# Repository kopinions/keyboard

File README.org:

* Keyboard

** 键盘布局
[[file:assets/imgs/layout.jpg]]

** 硬件

硬件部分主要包含电路原理图，以及电路板设计图。
** 软件（固件）

软件部分主要包含 基于 esp-idf 实现的 esp32 mcu 的键盘主控固件。

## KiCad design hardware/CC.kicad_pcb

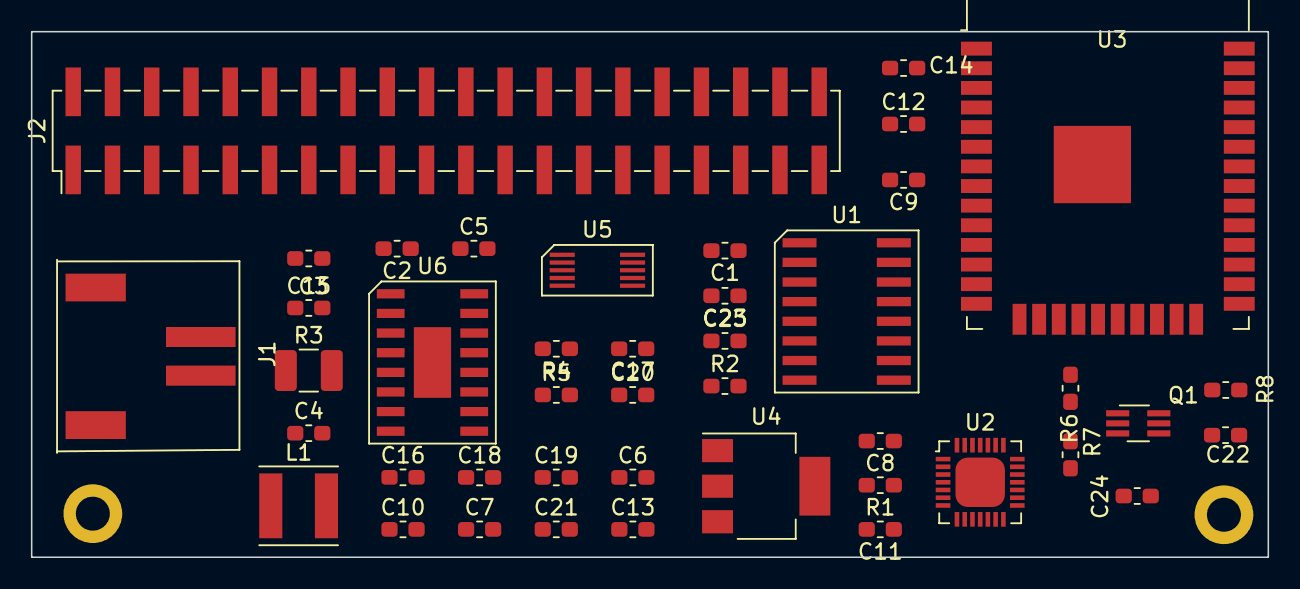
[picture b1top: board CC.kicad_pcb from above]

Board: 2 copper layers, 80.0 x 34.0 mm, 46 parts (1 on the bottom side), 55 nets, no tracks yet.

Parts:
C1: 103; C_0603_1608Metric_Pad1.05x0.95mm_HandSolder
C2, C5, C6, C7, C12, C17, C18, C23: 10uf; C_0603_1608Metric_Pad1.05x0.95mm_HandSolder
C3, C4, C8, C9, C10, C14, C16, C22, C24, C25: 104; C_0603_1608Metric_Pad1.05x0.95mm_HandSolder
C11: 4.7uf; C_0603_1608Metric_Pad1.05x0.95mm_HandSolder
C13: 2.2uf; C_0603_1608Metric_Pad1.05x0.95mm_HandSolder
C15: 4.7nf; C_0603_1608Metric_Pad1.05x0.95mm_HandSolder
C19, C20, C21: 22uf; C_0603_1608Metric_Pad1.05x0.95mm_HandSolder
H1, H2: MountingHole; MountingHole_2.2mm_M2_DIN965_Pad
J1: Conn_01x02_Female; JST_XH_S2B-XH-A-1_1x02_P2.50mm_Horizontal
J2: Conn_02x20_Odd_Even; PinHeader_2x20_P2.54mm_Vertical_SMD
L1: 1uH; L_5x5x2
Q1: Q_DUAL_NPN; SOT-363_SC-70-6_Handsoldering
R1: 22.1K; R_0603_1608Metric_Pad1.05x0.95mm_HandSolder
R2: 47.5K; R_0603_1608Metric_Pad1.05x0.95mm_HandSolder
R3: R010; R_1210_3225Metric_Pad1.42x2.65mm_HandSolder
R4: 2R0; R_0603_1608Metric_Pad1.05x0.95mm_HandSolder
R5: 102; R_0603_1608Metric_Pad1.05x0.95mm_HandSolder
R6, R7: 10K; R_0603_1608Metric_Pad1.05x0.95mm_HandSolder
R8: 10k; R_0603_1608Metric_Pad1.05x0.95mm_HandSolder
SW1: SW-2P; SW_DIP_SPSTx02_Slide_6.7x6.64mm_W8.61mm_P2.54mm_LowProfile
U1: CH9328
U2: CP2102N-A01-GQFN28; QFP-28_5x5_Pitch0.5mm
U3: ESP32-WROOM-32D; ESP32-WROOM-32
U4: AMS1117-3.3; SOT-223-3_TabPin2
U5: BL1530-DPDT; BL1530
U6: IP5108

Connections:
+BATT: C2.1, C3.1, J1.2, R3.2, U6.16
/ACT: U1.16, U3.22
/CAPS: J2.38, U3.20
/COL1: J2.13, U3.24
/COL2: J2.15, U3.26
/COL3: J2.17, U3.29
/COL4: J2.19, U3.14
/COL5: J2.21, U3.16
/COL6: J2.23, U3.13
/COL7: J2.25, U3.23
/COL8: J2.27, U3.27
/COL9: J2.29, U3.28
/COL10: J2.31, U3.30
/COL11: J2.33, U3.31
/COL12: J2.35, U3.33
/COL13: J2.37, U3.36
/COL14: J2.39, U3.37
/COL15: J2.40, U3.10
/DTR: Q1.4, R6.2, U2.28
/EN: C24.1, Q1.6, R8.2, SW1.3, U3.3
/FD+: U2.4, U5.2
/FD-: U2.5, U5.8
/FRXD: U2.25, U3.18
/FTXD: U2.26, U3.17
/IO0: C22.1, Q1.3, SW1.4, U3.25, U5.1
/KD+: U1.6, U5.3
/KD-: U1.7, U5.9
/KRXD: U1.3, U3.34
/KTXD: U1.2, U3.35
/L1: J2.6, U3.21, U6.9
/L2: J2.4, U3.5, U6.10
/L3: J2.2, U3.4, U6.11
/LX: C15.1, L1.2, U6.3, U6.4
/ROW1: J2.1, U3.11
/ROW2: J2.3, U3.12
/ROW3: J2.5, U3.8
/ROW4: J2.7, U3.9
/ROW5: J2.9, U3.6
/ROW6: J2.11, U3.7
/RTS: Q1.1, R7.2, U2.24
/SCLK: J2.36, U3.19
/USBD+: J2.32, U5.4
/USBD-: J2.30, U5.10
GND: C1.1, C2.2, C3.2, C4.2, C5.2, C6.2, C7.2, C8.1, C9.1, C10.2, C11.2, C12.2, C13.1, C14.1, C17.2, C20.2, C22.2, C23.2, C24.2, C25.1, J1.1, J2.10, J2.12, J2.14, J2.16, J2.18, J2.20, J2.22, J2.24, J2.26, J2.34, R2.2, R5.2, SW1.1, SW1.2, U1.8, U1.11, U2.3, U2.29, U3.1, U3.15, U3.38, U3.39, U4.1, U5.5, U5.7, U6.2, U6.8, U6.14, U6.15, U6.17
unnamed: C1.2, U1.5
unnamed: C4.1, C6.1, L1.1, R3.1, U6.1
unnamed: C5.1, R4.2
unnamed: C13.2, U6.12, U6.13
unnamed: C16.2, C18.2, C19.2, C21.2
unnamed: Q1.2, R6.1
unnamed: Q1.5, R7.1
unnamed: R1.2, R2.1, U2.8
VBUS: C7.1, C10.1, J2.28, R1.1, R4.1, R5.1, U6.7
VDD5V: C15.2, C16.1, C17.1, C18.1, C19.1, C21.1, U4.3, U6.5, U6.6
VDD33: C8.2, C9.2, C11.1, C12.1, C14.2, C20.1, C23.1, C25.2, J2.8, R8.1, U1.12, U1.13, U1.14, U1.15, U2.6, U2.7, U3.2, U4.2, U5.6

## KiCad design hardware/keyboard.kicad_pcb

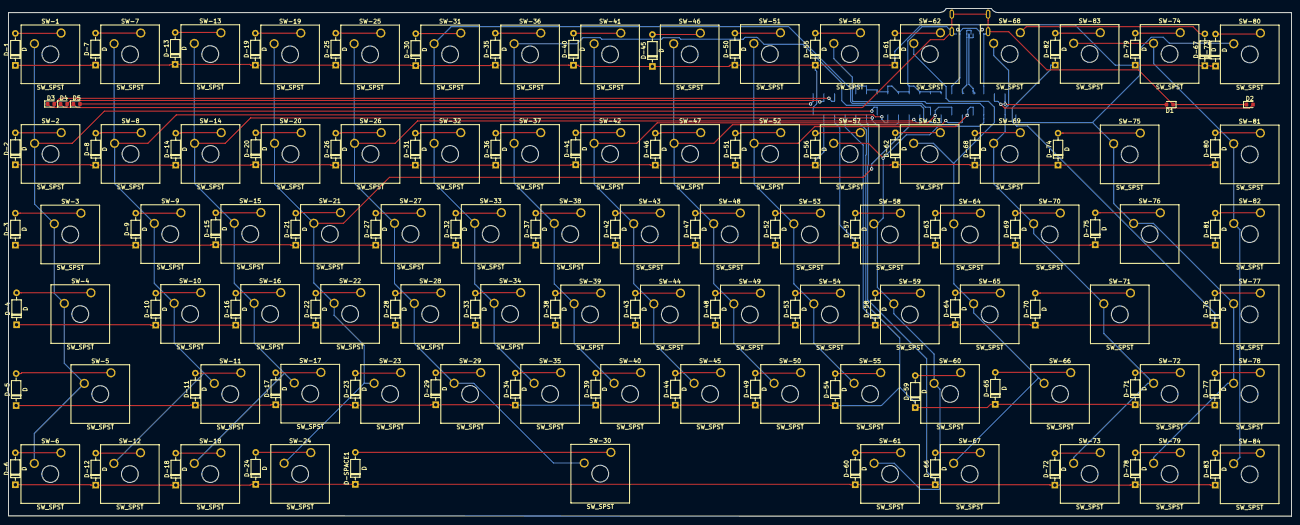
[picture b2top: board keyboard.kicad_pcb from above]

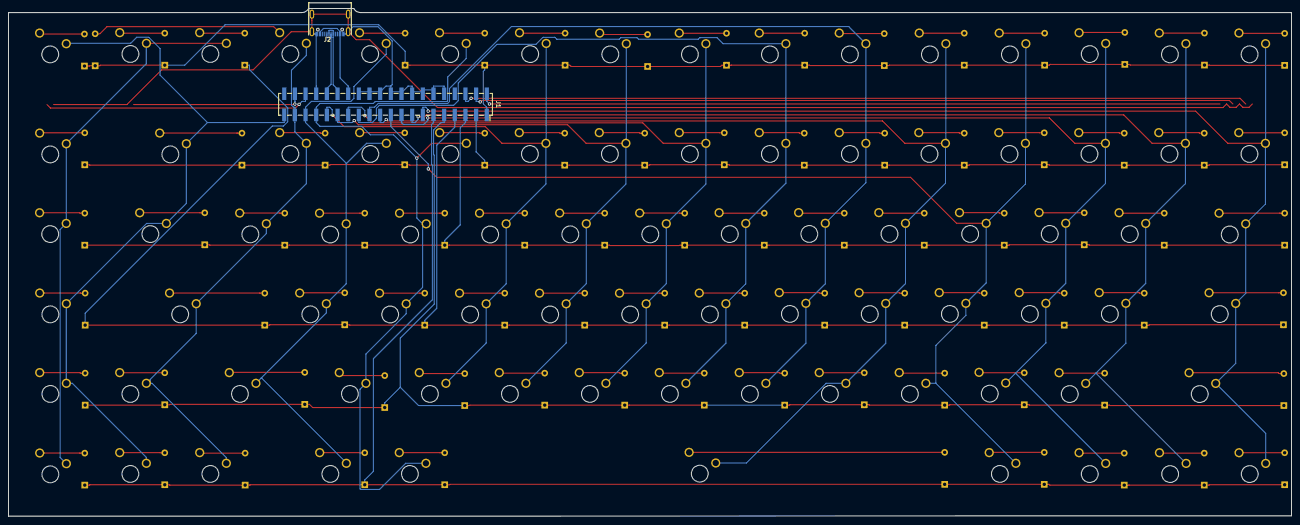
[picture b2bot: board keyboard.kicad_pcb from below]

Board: 2 copper layers, 305.7 x 121.0 mm, 175 parts (2 on the bottom side), 112 nets.

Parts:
D1, D2, D3, D4, D5: D; LED_0603_1608Metric
D-1, D-2, D-3, D-4, D-5, D-6, D-7, D-8, D-9, D-10, D-11, D-12, D-13, D-14, D-15, D-16, D-17, D-18, D-19, D-20, D-21, D-22, D-23, D-24, D-25, D-26, D-27, D-28, D-29, D-30, D-31, D-32, D-33, D-34, D-35, D-36, D-37, D-38, D-39, D-40, D-41, D-42, D-43, D-44, D-45, D-46, D-47, D-48, D-49, D-50, D-51, D-52, D-53, D-54, D-55, D-56, D-57, D-58, D-59, D-60, D-61, D-62, D-63, D-64, D-65, D-66, D-67, D-68, D-69, D-70, D-71, D-72, D-73, D-74, D-75, D-76, D-77, D-78, D-79, D-80, D-81, D-82, D-83: D; D_DO-35_SOD27_P7.62mm_Horizontal
D-SPACE1: D; D_DO-35_SOD27_P7.62mm_Horizontal
J1: Conn_02x20_Odd_Even; PinSocket_2x20_P2.54mm_Vertical_SMD
J2: USB_C_Receptacle_16P
SW-1, SW-2, SW-6, SW-7, SW-8, SW-9, SW-10, SW-11, SW-12, SW-13, SW-14, SW-15, SW-16, SW-17, SW-18, SW-19, SW-20, SW-21, SW-22, SW-23, SW-25, SW-26, SW-27, SW-28, SW-29, SW-31, SW-32, SW-33, SW-34, SW-35, SW-36, SW-37, SW-38, SW-39, SW-40, SW-41, SW-42, SW-43, SW-44, SW-45, SW-46, SW-47, SW-48, SW-49, SW-50, SW-51, SW-52, SW-53, SW-54, SW-55, SW-56, SW-57, SW-58, SW-59, SW-60, SW-61, SW-62, SW-63, SW-64, SW-65, SW-67, SW-68, SW-69, SW-70, SW-72, SW-73, SW-74, SW-77, SW-78, SW-79, SW-80, SW-81, SW-82, SW-83, SW-84: SW_SPST; SW_Cherry_MX_1.00u_Plate
SW-3, SW-76: SW_SPST; SW_Cherry_MX_1.50u_Plate
SW-4, SW-66: SW_SPST; SW_Cherry_MX_1.75u_Plate
SW-5, SW-71: SW_SPST; SW_Cherry_MX_2.25u_Plate
SW-24: SW_SPST; SW_Cherry_MX_1.25u_Plate
SW-30: SW_SPST; SW_Cherry_MX_6.25u_Plate
SW-75: SW_SPST; SW_Cherry_MX_2.00u_Plate

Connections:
/CAPS: D1.2, J1.38
/COL1: J1.13, SW-1.2, SW-2.2, SW-3.2, SW-4.2, SW-5.2, SW-6.2
/COL2: J1.15, SW-7.2, SW-8.2, SW-9.2, SW-10.2, SW-11.2, SW-12.2
/COL3: J1.17, SW-13.2, SW-14.2, SW-15.2, SW-16.2, SW-17.2, SW-18.2
/COL4: J1.19, SW-19.2, SW-20.2, SW-21.2, SW-22.2, SW-23.2, SW-24.2
/COL5: J1.21, SW-25.2, SW-26.2, SW-27.2, SW-28.2, SW-29.2, SW-30.2
/COL6: J1.23, SW-31.2, SW-32.2, SW-33.2, SW-34.2, SW-35.2
/COL7: J1.25, SW-36.2, SW-37.2, SW-38.2, SW-39.2, SW-40.2
/COL8: J1.27, SW-41.2, SW-42.2, SW-43.2, SW-44.2, SW-45.2
/COL9: J1.29, SW-46.2, SW-47.2, SW-48.2, SW-49.2, SW-50.2
/COL10: J1.31, SW-51.2, SW-52.2, SW-53.2, SW-54.2, SW-55.2
/COL11: J1.33, SW-56.2, SW-57.2, SW-58.2, SW-59.2, SW-60.2, SW-61.2
/COL12: J1.35, SW-62.2, SW-63.2, SW-64.2, SW-65.2, SW-66.2, SW-67.2
/COL13: J1.37, SW-68.2, SW-69.2, SW-70.2, SW-71.2, SW-72.2, SW-73.2
/COL14: J1.39, SW-74.2, SW-75.2, SW-76.2, SW-77.2, SW-78.2, SW-79.2
/COL15: SW-80.2, SW-81.2, SW-82.2, SW-83.2, SW-84.2
/ROW1: D-1.1, D-7.1, D-13.1, D-19.1, D-25.1, D-30.1, D-35.1, D-40.1, D-45.1, D-50.1, D-55.1, D-61.1, D-67.1, D-73.1, D-79.1, J1.1
/ROW2: D-2.1, D-8.1, D-14.1, D-20.1, D-26.1, D-31.1, D-36.1, D-41.1, D-46.1, D-51.1, D-56.1, D-62.1, D-68.1, D-74.1, D-80.1, J1.3
/ROW3: D-3.1, D-9.1, D-15.1, D-21.1, D-27.1, D-32.1, D-37.1, D-42.1, D-47.1, D-52.1, D-57.1, D-63.1, D-69.1, D-75.1, D-81.1, J1.5
/ROW4: D-4.1, D-10.1, D-16.1, D-22.1, D-28.1, D-33.1, D-38.1, D-43.1, D-48.1, D-53.1, D-58.1, D-64.1, D-70.1, D-76.1, D-82.1, J1.7
/ROW5: D-5.1, D-11.1, D-17.1, D-23.1, D-29.1, D-34.1, D-39.1, D-44.1, D-49.1, D-54.1, D-59.1, D-65.1, D-71.1, D-77.1, J1.9
/ROW6: D-6.1, D-12.1, D-18.1, D-24.1, D-60.1, D-66.1, D-72.1, D-78.1, D-83.1, D-SPACE1.1, J1.11
/SCLK: D2.2, J1.36
/USBD_N: J1.30, J2.A7, J2.B7
/USBD_P: J1.32, J2.A6, J2.B6
GND: D1.1, D2.1, D3.1, D4.1, D5.1, J1.10, J1.12, J1.14, J1.16, J1.18, J1.20, J1.22, J1.24, J1.26, J1.34, J2.A1, J2.B1, J2.S1
unnamed: D-1.2, SW-1.1
unnamed: D-2.2, SW-2.1
unnamed: D-3.2, SW-3.1
unnamed: D-4.2, SW-4.1
unnamed: D-5.2, SW-5.1
unnamed: D-6.2, SW-6.1
unnamed: D-7.2, SW-7.1
unnamed: D-8.2, SW-8.1
unnamed: D-9.2, SW-9.1
unnamed: D-10.2, SW-10.1
unnamed: D-11.2, SW-11.1
unnamed: D-12.2, SW-12.1
unnamed: D-13.2, SW-13.1
unnamed: D-14.2, SW-14.1
unnamed: D-15.2, SW-15.1
unnamed: D-16.2, SW-16.1
unnamed: D-17.2, SW-17.1
unnamed: D-18.2, SW-18.1
unnamed: D-19.2, SW-19.1
unnamed: D-20.2, SW-20.1
unnamed: D-21.2, SW-21.1
unnamed: D-22.2, SW-22.1
unnamed: D-23.2, SW-23.1
unnamed: D-24.2, SW-24.1
unnamed: D-25.2, SW-25.1
unnamed: D-26.2, SW-26.1
unnamed: D-27.2, SW-27.1
unnamed: D-28.2, SW-28.1
unnamed: D-29.2, SW-29.1
unnamed: D-30.2, SW-31.1
unnamed: D-31.2, SW-32.1
unnamed: D-32.2, SW-33.1
unnamed: D-33.2, SW-34.1
unnamed: D-34.2, SW-35.1
unnamed: D-35.2, SW-36.1
unnamed: D-36.2, SW-37.1
unnamed: D-37.2, SW-38.1
unnamed: D-38.2, SW-39.1
unnamed: D-39.2, SW-40.1
unnamed: D-40.2, SW-41.1
unnamed: D-41.2, SW-42.1
unnamed: D-42.2, SW-43.1
unnamed: D-43.2, SW-44.1
unnamed: D-44.2, SW-45.1
unnamed: D-45.2, SW-46.1
unnamed: D-46.2, SW-47.1
unnamed: D-47.2, SW-48.1
unnamed: D-48.2, SW-49.1
unnamed: D-49.2, SW-50.1
unnamed: D-50.2, SW-51.1
unnamed: D-51.2, SW-52.1
unnamed: D-52.2, SW-53.1
unnamed: D-53.2, SW-54.1
unnamed: D-54.2, SW-55.1
unnamed: D-55.2, SW-56.1
unnamed: D-56.2, SW-57.1
unnamed: D-57.2, SW-58.1
unnamed: D-58.2, SW-59.1
unnamed: D-59.2, SW-60.1
unnamed: D-60.2, SW-61.1
unnamed: D-61.2, SW-62.1
unnamed: D-62.2, SW-63.1
unnamed: D-63.2, SW-64.1
unnamed: D-64.2, SW-65.1
unnamed: D-65.2, SW-66.1
unnamed: D-66.2, SW-67.1
unnamed: D-67.2, SW-68.1
unnamed: D-68.2, SW-69.1
unnamed: D-69.2, SW-70.1
unnamed: D-70.2, SW-71.1
unnamed: D-71.2, SW-72.1
unnamed: D-72.2, SW-73.1
unnamed: D-73.2, SW-74.1
unnamed: D-74.2, SW-75.1
unnamed: D-75.2, SW-76.1
unnamed: D-76.2, SW-77.1
unnamed: D-77.2, SW-78.1
unnamed: D-78.2, SW-79.1
unnamed: D-79.2, SW-80.1
unnamed: D-80.2, SW-81.1
unnamed: D-81.2, SW-82.1
unnamed: D-82.2, SW-83.1
unnamed: D-83.2, SW-84.1
unnamed: D-SPACE1.2, SW-30.1
VBUS: J1.28, J2.A4, J2.B4
VDD33: J1.2, J1.4, J1.6, J1.8

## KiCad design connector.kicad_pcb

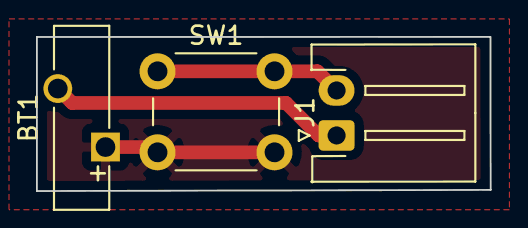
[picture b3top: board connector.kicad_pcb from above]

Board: 2 copper layers, 25.2 x 8.6 mm, 3 parts (0 on the bottom side), 3 nets.

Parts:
BT1: Battery_Cell; Battery_Panasonic_CR1025-VSK_Vertical_CircularHoles
J1: Conn_01x02; JST_XH_S2B-XH-A-1_1x02_P2.50mm_Horizontal
SW1: SW_Push; SW_PUSH_6mm_H9.5mm

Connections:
unnamed: BT1.1, SW1.2
unnamed: BT1.2, J1.1
unnamed: J1.2, SW1.1

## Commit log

2020-08-19 feat: init the keyboard files
2020-08-20 feat: update the pin socket to 2.54 mm
2020-08-21 feat: change the pin socket to 2.54mm
2020-08-24 feat: add battery indicator and change the pin socket layout
2020-08-24 fix: fix the pinsocket and pinheader config
2020-08-27 feat: change the 2 pin connector from jst ph to jst xh
2020-08-27 feat: change the typec from 24 pin to 16 pin
2020-08-27 feat: update the typec footprint
2020-09-02 feat: change global label to label
2020-09-22 feat: update the jst package
2020-09-24 feat: rerouting the cc and keyboard
2020-09-24 feat: update the routing for the differential pair
2020-09-24 feat: update differential skew
2020-09-24 feat: add fabrication files
2020-09-28 build: move all the pcb related to hardware
2020-09-28 feat: init the software project
2020-09-29 feat: build up project skeleton
2020-10-16 feat(main): init the main dir
2020-10-17 fix(main): declare app_main function
2020-10-17 build: add clang-format support
2020-10-19 feat: add custom test framework
2020-10-20 fix: seprate the tests with esp code
2020-10-20 feat: add keyboard releated
2020-10-20 feat: add fakeit dependence
2020-10-20 feat: add expect_that support
2020-10-20 feat: enable fakeit
2020-10-21 feat: integrate with di
2020-10-21 feat: add keyboard related domain
2020-10-22 fix: illegal instruction caused by no return vector result
2020-10-22 feat: integrate all components
2020-10-22 refactor: change the units folder structor
2020-10-26 feat: add matrix test
2020-10-26 feat: should init the matrix
2020-10-26 build: should able to build to esp32
2020-10-26 build: build test and units both ok
2020-10-27 refactor: config via command line args and env
2020-10-27 doc: add software readme
2020-10-27 doc: add readme
2020-10-27 feat: should able to scan by pin status
2020-10-27 feat: should able to scan the matrix for 2 row 2 col
2020-10-27 refactor: change the test framework
2020-10-27 feat: output the var args
2020-10-27 refactor: output enum value
2020-10-27 build: make di as source dep
2020-10-28 fix: fix compile problem
2020-10-28 feat: should able to debounce the matrix
2020-10-29 refactor: use map for matrix scan result
2020-10-29 feat: should able to compile the kbd.elf
2020-10-29 refactor: move all class to namespace kopinions
2020-10-30 feat: add task related
2020-10-30 feat: integrate with esp-idf api
2020-10-30 feat: integrate with esp-idf freertos
2020-10-31 feat: add log module
2020-10-31 refactor: refactor logger
2020-10-31 feat: add key mapping table
2020-10-31 fix: test fix by extract mapping module
2020-11-02 feat: add dumy layout test
2020-11-02 feat(hardware): update kbd layout
2020-11-02 feat: change flash size to 4mb
2020-11-03 feat: add tasks test
2020-11-04 refactor: add functionals
2020-11-05 fix: fix the function test
2020-11-05 style: add style related task and reformat
2020-11-05 style: always reformat changed files
2020-11-05 feat: fullfile the fakes
2020-11-05 feat: should able to find the key pressed by layout
2020-11-11 refactor: extract custom task function
2020-11-11 feat: schedule the task
2020-11-13 fix: fix the schedule test
2020-11-16 fix: use col base scan method to fix the 34 & 35 is input only port
2020-11-16 doc: update software readme
2020-11-20 fix: try to fix schedule function not called
2020-11-23 fix: layout can not be found while using the virtual scan method
2020-11-24 fix: esp log fix
2020-11-25 fix: try to fix the matrix config injector error
2020-11-27 refactor: remove the di for the kbd main
2020-11-30 feat(hardware): update the ip5206 to ip5108 and change the bl1530 footprint
2020-12-03 feat(softward): add unity based test
2020-12-04 feat: add qfn 28
2020-12-07 feat: add unit test with uity
2020-12-07 build: remove sdkconfig.old from git history
2020-12-07 feat: add keyboard layout
2020-12-08 feat(hardward): add quad flat package 28 for cp2102
2020-12-09 feat: update cc layout
2020-12-17 feat: add ble and hid
2020-12-18 fix: try to fix gatt
2020-12-21 feat: try to extract bt profile
2020-12-21 feat: add repo template
2020-12-22 feat: ble can register profile
2020-12-23 feat: add demo gatt profile
2020-12-24 feat: should able to register app
2020-12-24 feat: should the esp ble provision find the ble device
2020-12-25 feat: should able to save the service and connection id
2020-12-25 feat: add dummy hid
2020-12-31 feat: add basic hid releated
2021-01-02 build: build fix
2021-01-04 feat: add dummy hid profile
2021-01-06 refactor: extract the ble spec
2021-01-12 feat: add visitor pattern for the service and application and attribute
2021-01-21 feat: extract vistior and gatt_if
2021-01-22 feat: should register application to the ble
2021-01-22 feat: should able to adv the application
2021-01-23 feat: make the name as the ble device name
2021-01-23 fix: should able to call the application notified without error
2021-01-25 refactor: make the esp_if impl seprate from hpp(cause duplication declaration)
2021-01-25 feat: add bt phase for the application handle
2021-01-25 feat: add profile builder
2021-01-26 feat: use builder to construct the profile service and application
2021-01-26 feat: should able to build the profiles to the application
2021-01-26 feat: should able to visit the profile services
2021-01-26 refactor: seprate the builders and visitors
2021-01-26 refactor: add characteristic builder
2021-01-27 feat: should the attirbute visitor create attritube table
2021-01-27 refactor: visitor cast with decltype
2021-01-27 feat: should able to create attributes
2021-01-28 fix: fix the create attribute error with wrong max attributes size
2021-01-28 feat: characterisitic builder add property and permission
2021-01-29 feat: add value and property and permission def inside characteristic
2021-01-30 feat: add value and length releated
2021-02-18 fix: characteristic builder build with data
2021-02-18 fix: try to fix the bt core dump
2021-02-18 feat: bt log on verbose
2021-04-21 refactor: move the scheduler cpp impl to the hpp
2021-05-31 feat: add direnv config
2021-06-02 feat: update the env config
2021-06-03 feat: add logger format
2021-06-03 feat: init the nvs in the appmain
2021-06-03 feat: change shared ptr to raw pointer
2021-06-04 feat: add custom heap failed callback
2021-06-07 fix: the bluttooth app can be runed under esp32
2021-06-07 fix: the character uuid len
2021-06-08 feat: add stringify for the spec
2021-06-08 fix: try to fix bug
2021-06-15 fix: A stack overflow in task BTC_TASK has been detected
2021-06-15 fix: the event type is not transferd to the notified
2021-06-18 fix: should abel to start gap
2021-06-20 refactor: change the variable local
2021-06-22 feat: send response for the read request(automate=false)
2021-06-22 refactor: use the attribute visitor method
2021-07-06 refactor: use the uint16 as length type instead size_t
2021-07-06 feat: change the appid to identify as hid device
2021-07-06 refactor: change the application id to enum
2021-07-06 build: update the sdkconfig
2021-07-07 feat: add all the keyboard characteristic
2021-07-07 refactor: use scheduler to start the task
2021-07-10 refactor: change the builder interface
2021-07-13 refactor: change the builder to buile the attribute from heap
2021-07-13 refactor: construct the service with new builder interface
2021-07-13 feat: handle the battery and hid register
2021-07-15 refactor: build the application and profile to pointer
2021-07-15 feat: add keyboard related report
2021-07-16 fix: the feature can be duplicated with the enum class
2021-07-22 fix: the task should not end
2021-07-22 feat: merge the two services to the profiles
2021-07-23 refactor: remvoe unused codes
2021-07-23 refactor: dump with correct indent
2021-07-23 feat: should able to update the handles while register to the esp gattserver
2021-07-23 fix: fix the builders
2021-07-24 feat: add include builder
2021-07-27 fix: automated miss config
2021-07-27 fix: some character declare
2021-07-27 feat: should able to register the included service
2021-07-28 feat: should able create service by dependience
2021-07-29 refactor: refactor the app register
2021-07-29 fix: the applcation profile fix
2021-08-02 fix: all handle could be get
2021-08-02 feat: pair with other device
2021-08-03 refactor: set the descriptor via the descriptor builder
2021-08-03 refactor: inline send report func
2021-08-03 refactor: refactor and fix the end handle not correctly handled
2021-08-03 feat: send data to the device
2021-08-03 feat: temp make send data
2021-08-03 feat: able to send the indicate to the device
2021-08-04 refactor: move the sedn insdicate to the gatt interface
2021-08-04 refactor: save the connection id to gattif
2021-08-04 refactor: remove unused codes
2021-08-11 feat: update the hid keycodes according USB HID Usage Tables Keyboard
2021-08-11 fix: select correct pin to scan
2021-08-13 refactor: update the file structure
2021-08-13 refactor: move file to include dir for vif
2021-08-16 refactor: renmae key to key_t
2021-08-16 feat: add sedes for supporting the transform
2021-08-17 feat: add sedes tests
2021-08-17 refactor: use the idf as lib
2021-08-17 feat: add the stubs
2021-08-18 refactor: add fake bt
2021-08-18 build: all components as library
2021-08-18 build: seprate the include and src
2021-08-19 fix: fix compile error
2021-08-19 fix: link the kbd.elf
2021-08-19 build: should able to build with esp32 target
2021-08-19 feat: enable tests
2021-08-20 feat: add supporting tests sedes
2021-08-20 feat: should seralize multiple special keys
2021-08-20 feat: should abel to handle the special key release
2021-08-20 feat: should able to serial the normal keys
2021-08-20 refactor: make the modifiers member variable
2021-08-20 feat: add scripts to flash and monitor
2021-08-20 feat: send keys in kbd
2021-08-21 build: build before flash
2021-08-21 fix: sedes not existed to zero
2021-08-21 feat: should able only encode the pressed keys
2021-08-21 build: add build scripts
2021-08-21 feat: should able to send alt-space
2021-08-21 refactor: opt the scripts
2021-08-23 feat: enable all unit tests
2021-08-23 feat: add link
2021-08-23 fix: send indicate with non const pointer
2021-08-23 fix: the tests
2021-08-24 refactor: use the injector to create config
2021-08-24 refactor: use injector to create keyboard
2021-08-24 feat: make the ihid as injector module
2021-08-24 fix: inject application builder as singleton
2021-08-25 fix: inject the definitions of ble
2021-08-26 fix: should able to scan the io34 35 as input
2021-08-26 refactor: clean the codes
2021-08-26 feat: detect the keys
2021-08-26 feat: update log for changed key
2021-08-27 feat: pull all the pin down
2021-08-30 feat: should bypass left non modifier keys after six keys
2021-08-30 feat: make matrix config copyable
2021-08-31 fix: fix the conf test
2021-08-31 feat: add modifier
2021-08-31 fix: temp fix the injection
2021-09-01 fix: simple the modifer for compile
2021-09-03 feat: should modify the key accoding the mode
2021-09-03 refactor: extract the guardian
2021-09-07 feat: should able to construct the modifiers
